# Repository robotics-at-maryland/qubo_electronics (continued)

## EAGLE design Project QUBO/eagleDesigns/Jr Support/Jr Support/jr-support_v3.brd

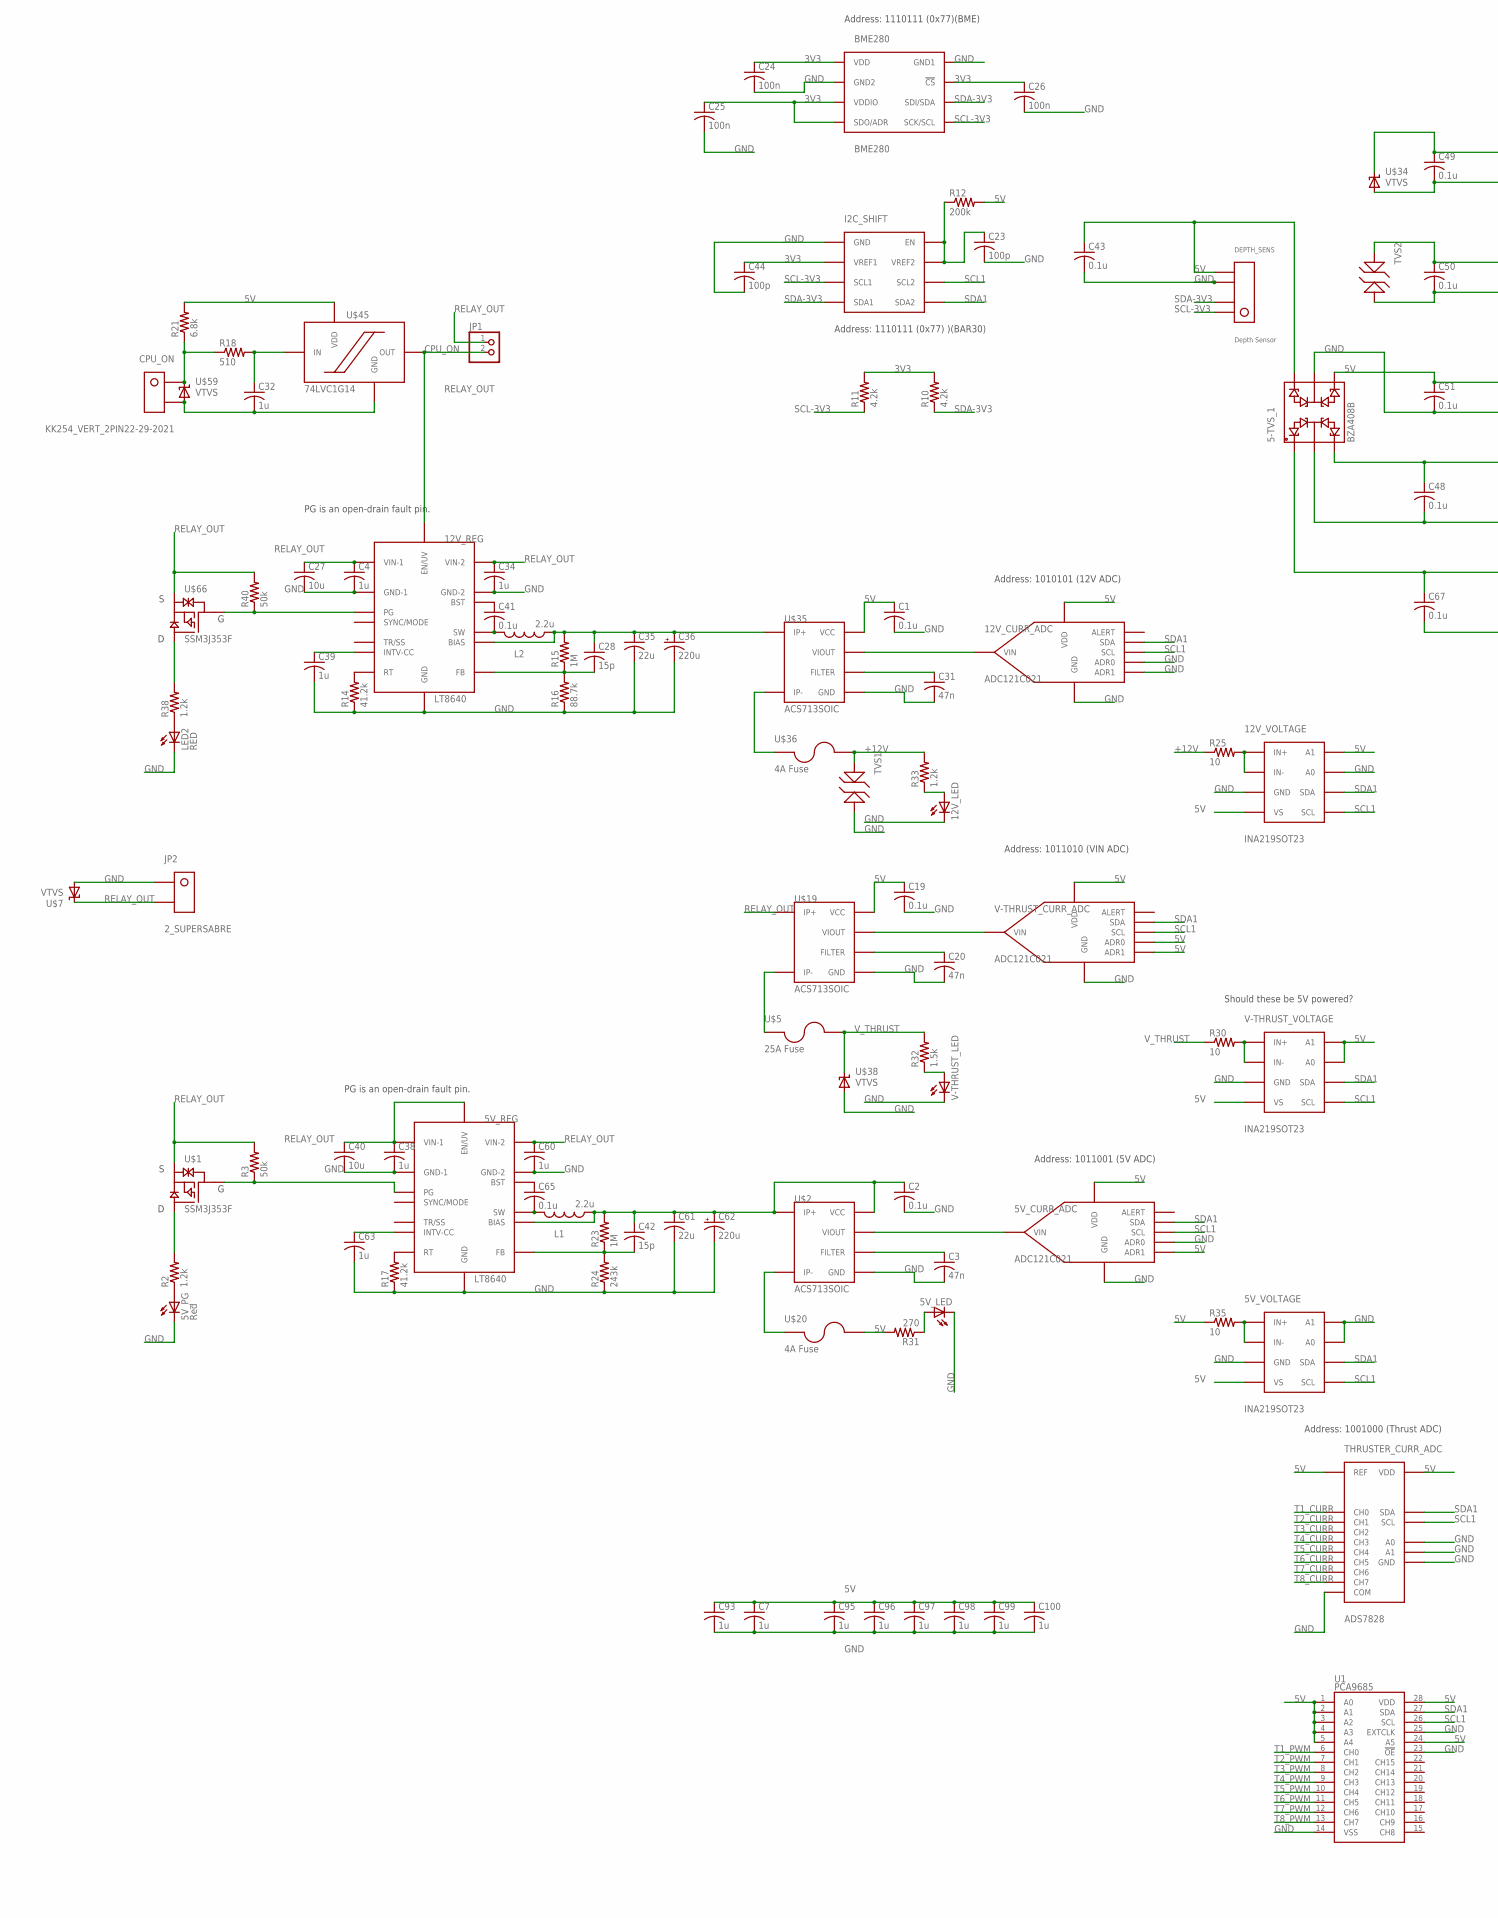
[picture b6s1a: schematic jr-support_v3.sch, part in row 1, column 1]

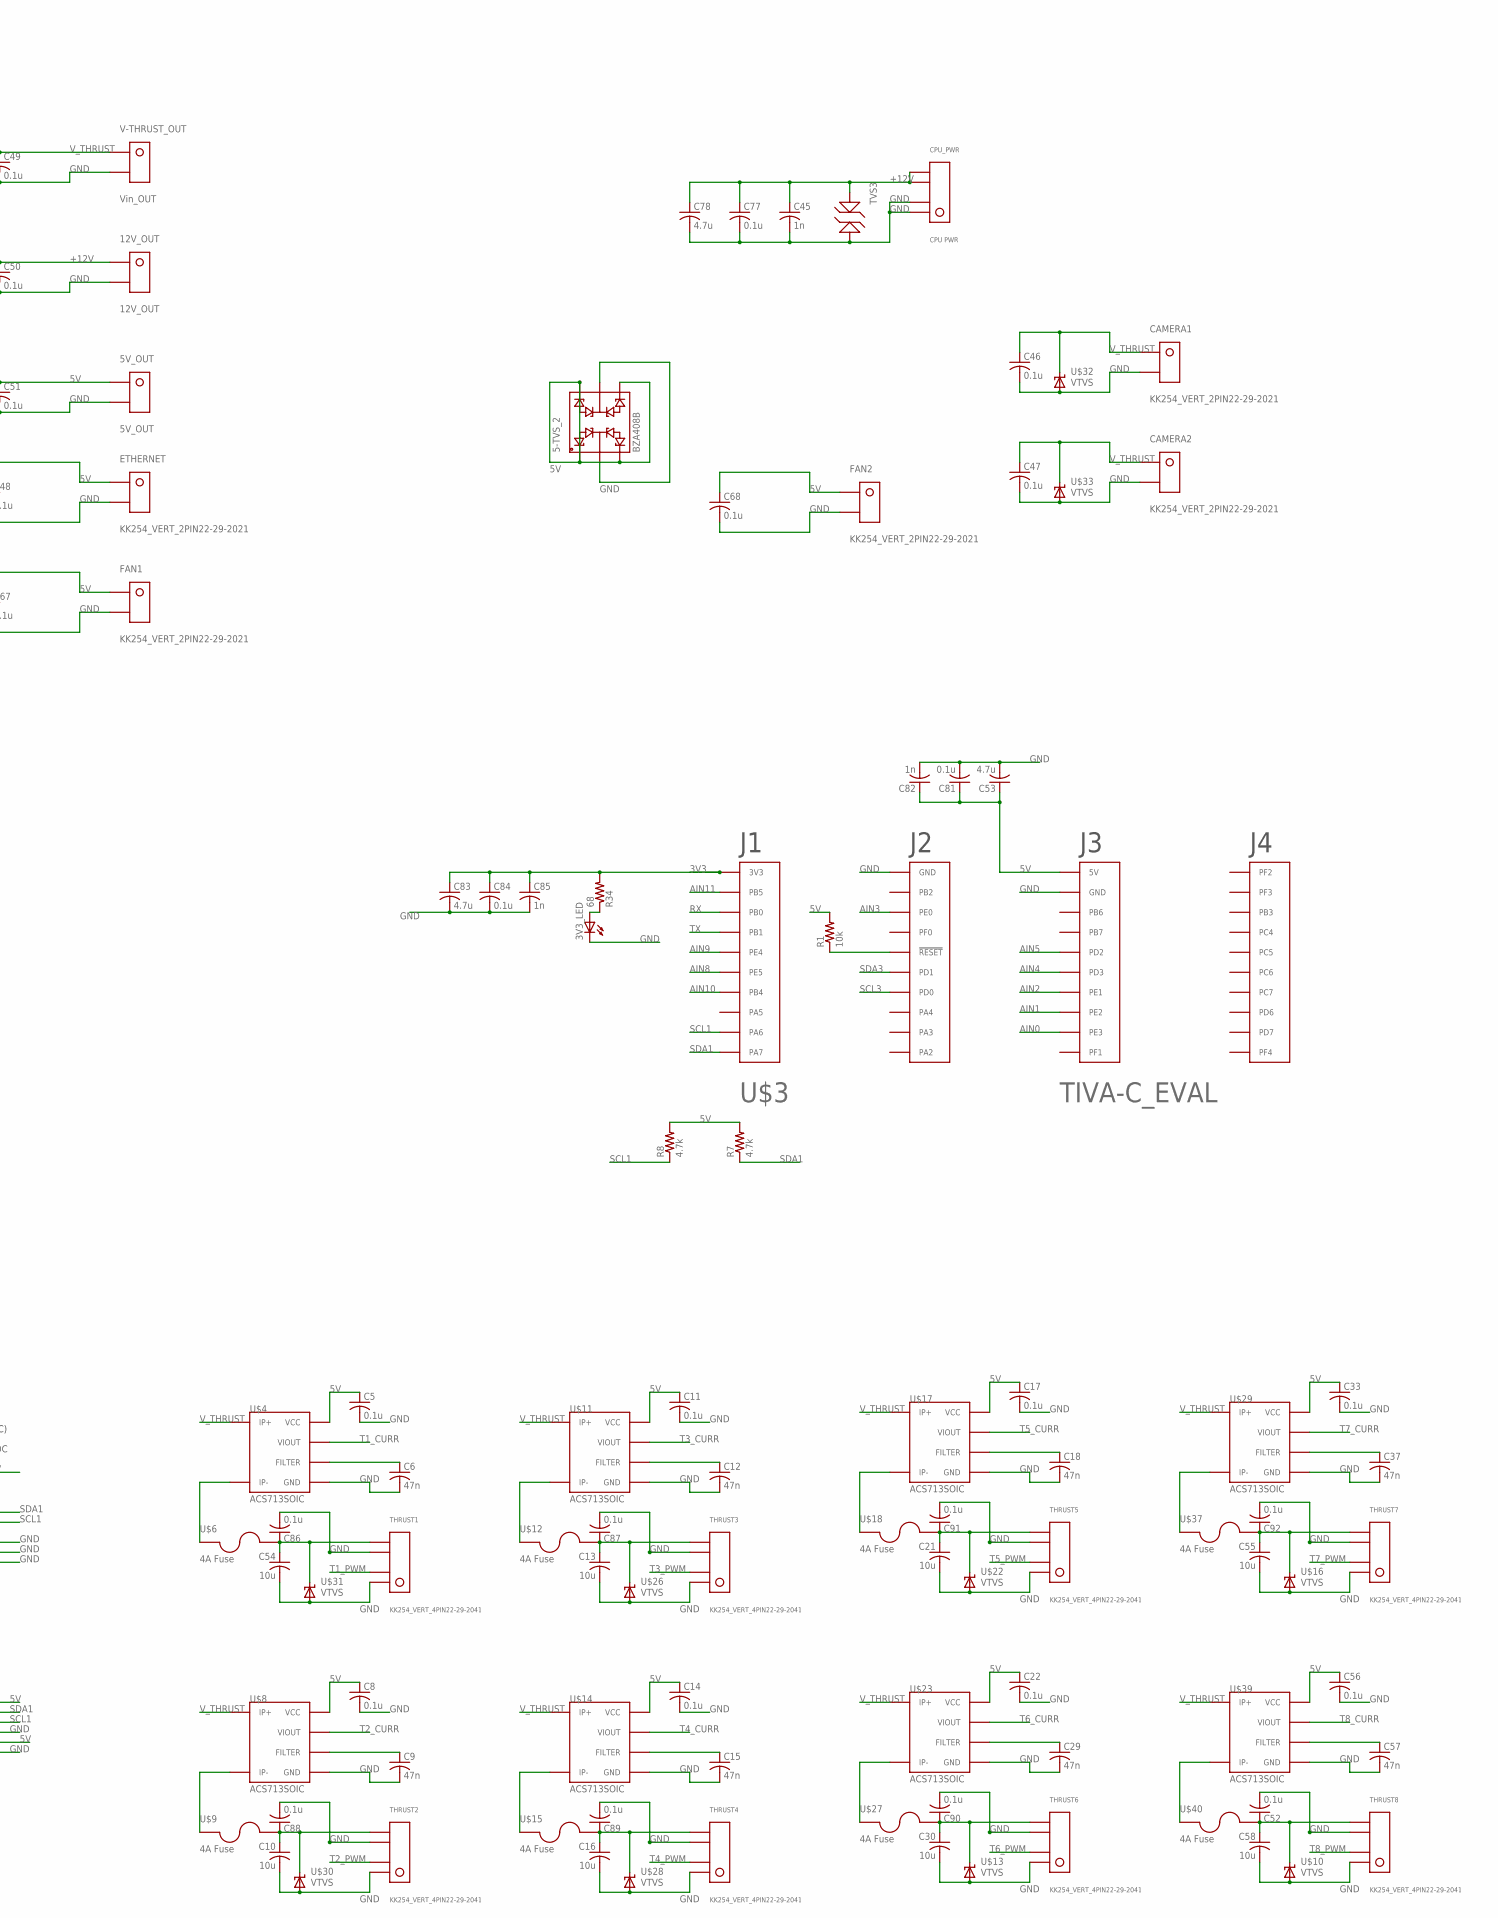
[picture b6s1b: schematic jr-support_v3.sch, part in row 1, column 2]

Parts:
3V3_LED, 5V_LED, 12V_LED: 0805_LED; 0805
5-TVS_1, 5-TVS_2: BZA408B; SOT457
5V_CURR_ADC, 12V_CURR_ADC: ADC121C021; VSSOP-8
5V_OUT: 5V_OUT; KK254_VERT_2PIN
5V_PG: Red; CHIP-LED0805
5V_REG, 12V_REG: LT8640; QFN18-3X4
5V_VOLTAGE, 12V_VOLTAGE: INA219SOT23; SOT-23-8
12V_OUT: 12V_OUT; KK254_VERT_2PIN
BME280: BME280; BME280_LGA
C1, C2, C5, C8, C11, C14, C17, C19, C22, C33, C41, C43, C46, C47, C48, C49, C50, C51, C52, C56, C65, C67, C68, C77, C81, C84, C86, C87, C88, C89, C90, C91, C92: 0.1u; C0805
C3, C6, C9, C12, C15, C18, C20, C29, C31, C37, C57: 47n; C0805
C4, C7, C32, C34, C38, C39, C60, C63, C93, C95, C96, C97, C98, C99, C100: 1u; C0805
C10, C13, C16, C21, C27, C30, C40, C54, C55, C58: 10u; C0805
C23, C44: 100p; C0805
C24, C25, C26: 100n; C0805
C28, C42: 15p; C0805
C35, C61: 22u; C0805
C36, C62: 220u; C-F80
C45, C82, C85: 1n; C0805
C53, C78, C83: 4.7u; C0805
CAMERA1, CAMERA2: KK254_VERT_2PIN22-29-2021; KK254_VERT_2PIN
CPU_ON: KK254_VERT_2PIN22-29-2021; KK254_VERT_2PIN
CPU_PWR: CPU PWR; KK254_VERT_4PIN
DEPTH_SENS: Depth Sensor; KK254_VERT_4PIN
ETHERNET: KK254_VERT_2PIN22-29-2021; KK254_VERT_2PIN
FAN1, FAN2: KK254_VERT_2PIN22-29-2021; KK254_VERT_2PIN
I2C_SHIFT: PCA9306DCT; SM8
JP1: PINHD-1X2; 1X02
JP2: 2_SUPERSABRE; SUPERSABRE_2CIRCUIT
L1, L2: 2.2u; L0740
LED2: RED; CHIP-LED0805
R1: 10k; R0805
R2, R33, R38: 1.2k; R0805
R3, R40: 50k; R0805
R7, R8: 4.7k; R0805
R10, R11: 4.2k; R0805
R12: 200k; R0805
R14, R17: 41.2k; R0805
R15, R23: 1M; R0805
R16: 88.7k; R0805
R18: 510; R0805
R21: 6.8k; R0805
R24: 243k; R0805
R25, R30, R35: 10; R0805
R31: 270; R0805
R32: 1.5k; R0805
R34: 68; R0805
THRUST1, THRUST2, THRUST3, THRUST4, THRUST5, THRUST6, THRUST7, THRUST8: KK254_VERT_4PIN22-29-2041; KK254_VERT_4PIN
THRUSTER_CURR_ADC: ADS7828; TSSOP16
TVS1, TVS2, TVS3: ESD12VD3B; SOD-323
U1: PCA9685; TSSOP-28_4MM
U$1, U$66: SSM3J353F; SOT-346-3/S-MINI
U$2, U$4, U$8, U$11, U$14, U$17, U$19, U$23, U$29, U$35, U$39: ACS713SOIC; ACS713-SOIC
U$3: TIVA-C_EVAL
U$5: 25A Fuse; 1.25"_FUSECLIPS
U$6, U$9, U$12, U$15, U$18, U$20, U$27, U$36, U$37, U$40: 4A Fuse; 154-OMNI-BLOK
U$7, U$10, U$13, U$16, U$22, U$26, U$28, U$30, U$31, U$32, U$33, U$34, U$38, U$59: VTVS; DO-219AB
U$45: 74LVC1G14; TSSOP5
V-THRUST_CURR_ADC: ADC121C021; VSSOP-8
V-THRUST_LED: 0805_LED; 0805
V-THRUST_OUT: Vin_OUT; KK254_VERT_2PIN
V-THRUST_VOLTAGE: INA219SOT23; SOT-23-8

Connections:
3V3: BME280.P$2 (!CS), BME280.P$5 (SDO/ADR), BME280.P$6 (VDDIO), BME280.P$8 (VDD), C24.1, C25.1, C26.1, C44.1, C83.1, C84.1, C85.1, I2C_SHIFT.P$2 (VREF1), R10.2, R11.2, R34.2, U$3.1-1 (3V3)
5V: 5-TVS_1.P$1, 5-TVS_1.P$3, 5-TVS_1.P$4, 5-TVS_1.P$6, 5-TVS_2.P$1, 5-TVS_2.P$3, 5-TVS_2.P$4, 5-TVS_2.P$6, 5V_CURR_ADC.P$5 (VDD), 5V_CURR_ADC.P$6 (ADR1), 5V_OUT.P$1, 5V_VOLTAGE.P$4 (VS), 12V_CURR_ADC.P$5 (VDD), 12V_VOLTAGE.P$4 (VS), 12V_VOLTAGE.P$8 (A1), C1.1, C5.1, C7.1, C8.1, C11.1, C14.1, C17.1, C19.1, C22.1, C33.1, C43.1, C48.1, C51.1, C53.1, C56.1, C67.1, C68.1, C81.1, C82.1, C93.1, C95.1, C96.1, C97.1, C98.1, C99.1, C100.1, DEPTH_SENS.P$4, ETHERNET.P$1, FAN1.P$1, FAN2.P$1, R1.2, R7.2, R8.2, R12.2, R21.2, R31.2, R35.1, THRUSTER_CURR_ADC.10 (REF), THRUSTER_CURR_ADC.16 (VDD), U1.1 (A0), U1.2 (A1), U1.3 (A2), U1.4 (A3), U1.5 (A4), U1.24 (A5), U1.28 (VDD), U$3.3-1 (5V), U$4.P$8 (VCC), U$8.P$8 (VCC), U$11.P$8 (VCC), U$14.P$8 (VCC), U$17.P$8 (VCC), U$19.P$8 (VCC), U$20.P$2, U$23.P$8 (VCC), U$29.P$8 (VCC), U$35.P$8 (VCC), U$39.P$8 (VCC), U$45.P$5 (VDD), V-THRUST_CURR_ADC.P$3 (ADR0), V-THRUST_CURR_ADC.P$5 (VDD), V-THRUST_CURR_ADC.P$6 (ADR1), V-THRUST_VOLTAGE.P$4 (VS), V-THRUST_VOLTAGE.P$7 (A0), V-THRUST_VOLTAGE.P$8 (A1)
+12V: 12V_OUT.P$1, C45.1, C50.1, C77.1, C78.1, CPU_PWR.P$3, CPU_PWR.P$4, R25.1, R33.2, TVS1.P$1, TVS2.P$1, TVS3.P$1, U$36.P$2
AIN0: U$3.3-9 (PE3)
AIN1: U$3.3-8 (PE2)
AIN2: U$3.3-7 (PE1)
AIN3: U$3.2-3 (PE0)
AIN4: U$3.3-6 (PD3)
AIN5: U$3.3-5 (PD2)
AIN8: U$3.1-6 (PE5)
AIN9: U$3.1-5 (PE4)
AIN10: U$3.1-7 (PB4)
AIN11: U$3.1-2 (PB5)
CPU_ON: 12V_REG.14 (EN/UV), JP1.2, U$45.P$4 (OUT)
GND: 3V3_LED.P$2 (C), 5-TVS_1.P$2, 5-TVS_1.P$5, 5-TVS_2.P$2, 5-TVS_2.P$5, 5V_CURR_ADC.P$3 (ADR0), 5V_CURR_ADC.P$7 (GND), 5V_LED.P$2 (C), 5V_OUT.P$2, 5V_PG.C, 5V_REG.6 (GND-1), 5V_REG.7 (GND-1), 5V_REG.10 (GND-2), 5V_REG.11 (GND-2), 5V_REG.18 (GND), 5V_VOLTAGE.P$3 (GND), 5V_VOLTAGE.P$7 (A0), 5V_VOLTAGE.P$8 (A1), 12V_CURR_ADC.P$3 (ADR0), 12V_CURR_ADC.P$6 (ADR1), 12V_CURR_ADC.P$7 (GND), 12V_LED.P$2 (C), 12V_OUT.P$2, 12V_REG.6 (GND-1), 12V_REG.7 (GND-1), 12V_REG.10 (GND-2), 12V_REG.11 (GND-2), 12V_REG.18 (GND), 12V_VOLTAGE.P$3 (GND), 12V_VOLTAGE.P$7 (A0), BME280.P$1 (GND1), BME280.P$7 (GND2), C1.2, C2.2, C3.2, C4.2, C5.2, C6.2, C7.2, C8.2, C9.2, C10.2, C11.2, C12.2, C13.2, C14.2, C15.2, C16.2, C17.2, C18.2, C19.2, C20.2, C21.2, C22.2, C23.2, C24.2, C25.2, C26.2, C27.2, C29.2, C30.2, C31.2, C32.2, C33.2, C34.2, C35.2, C36.P$2 (-), C37.2, C38.2, C39.2, C40.2, C43.2, C44.2, C45.2, C46.2, C47.2, C48.2, C49.2, C50.2, C51.2, C52.2, C53.2, C54.2, C55.2, C56.2, C57.2, C58.2, C60.2, C61.2, C62.P$2 (-), C63.2, C67.2, C68.2, C77.2, C78.2, C81.2, C82.2, C83.2, C84.2, C85.2, C86.2, C87.2, C88.2, C89.2, C90.2, C91.2, C92.2, C93.2, C95.2, C96.2, C97.2, C98.2, C99.2, C100.2, CAMERA1.P$2, CAMERA2.P$2, CPU_ON.P$2, CPU_PWR.P$1, CPU_PWR.P$2, DEPTH_SENS.P$3, ETHERNET.P$2, FAN1.P$2, FAN2.P$2, I2C_SHIFT.P$1 (GND), JP2.P$1, LED2.C, R14.1, R16.1, R17.1, R24.1, THRUST1.P$1, THRUST1.P$3, THRUST2.P$1, THRUST2.P$3, THRUST3.P$1, THRUST3.P$3, THRUST4.P$1, THRUST4.P$3, THRUST5.P$1, THRUST5.P$3, THRUST6.P$1, THRUST6.P$3, THRUST7.P$1, THRUST7.P$3, THRUST8.P$1, THRUST8.P$3, THRUSTER_CURR_ADC.9 (GND), THRUSTER_CURR_ADC.11 (COM), THRUSTER_CURR_ADC.12 (A0), THRUSTER_CURR_ADC.13 (A1), TVS1.P$2, TVS2.P$2, TVS3.P$2, U1.14 (VSS), U1.23 (!OE), U1.25 (EXTCLK), U$2.P$5 (GND), U$3.2-1 (GND), U$3.3-2 (GND), U$4.P$5 (GND), U$7.P$1 (A), U$8.P$5 (GND), U$10.P$1 (A), U$11.P$5 (GND), U$13.P$1 (A), U$14.P$5 (GND), U$16.P$1 (A), U$17.P$5 (GND), U$19.P$5 (GND), U$22.P$1 (A), U$23.P$5 (GND), U$26.P$1 (A), U$28.P$1 (A), U$29.P$5 (GND), U$30.P$1 (A), U$31.P$1 (A), U$32.P$1 (A), U$33.P$1 (A), U$34.P$1 (A), U$35.P$5 (GND), U$38.P$1 (A), U$39.P$5 (GND), U$45.P$3 (GND), U$59.P$1 (A), V-THRUST_CURR_ADC.P$7 (GND), V-THRUST_LED.P$2 (C), V-THRUST_OUT.P$2, V-THRUST_VOLTAGE.P$3 (GND)
unnamed: 12V_REG.15 (RT), R14.2
unnamed: R1.1, U$3.2-5 (!RESET!)
unnamed: 5V_PG.A, R2.1
unnamed: R2.2, U$1.P$2 (D)
unnamed: 5V_REG.19 (PG), R3.1, U$1.P$1 (G)
unnamed: 12V_REG.1 (BIAS), C28.1, C35.1, C36.P$1 (+), L2.P$2 (2), R15.2, U$35.P$1 (IP+), U$35.P$2 (IP+)
unnamed: 5V_REG.15 (RT), R17.2
unnamed: C3.1, U$2.P$6 (FILTER)
unnamed: C9.1, U$8.P$6 (FILTER)
unnamed: C6.1, U$4.P$6 (FILTER)
unnamed: C54.1, C86.1, THRUST1.P$4, U$6.P$2, U$31.P$2 (C)
unnamed: U$4.P$3 (IP-), U$4.P$4 (IP-), U$6.P$1
unnamed: C10.1, C88.1, THRUST2.P$4, U$9.P$2, U$30.P$2 (C)
unnamed: U$8.P$3 (IP-), U$8.P$4 (IP-), U$9.P$1
unnamed: C12.1, U$11.P$6 (FILTER)
unnamed: C13.1, C87.1, THRUST3.P$4, U$12.P$2, U$26.P$2 (C)
unnamed: U$11.P$3 (IP-), U$11.P$4 (IP-), U$12.P$1
unnamed: C15.1, U$14.P$6 (FILTER)
unnamed: C16.1, C89.1, THRUST4.P$4, U$15.P$2, U$28.P$2 (C)
unnamed: U$14.P$3 (IP-), U$14.P$4 (IP-), U$15.P$1
unnamed: C18.1, U$17.P$6 (FILTER)
unnamed: C21.1, C91.1, THRUST5.P$4, U$18.P$2, U$22.P$2 (C)
unnamed: U$17.P$3 (IP-), U$17.P$4 (IP-), U$18.P$1
unnamed: C29.1, U$23.P$6 (FILTER)
unnamed: C30.1, C90.1, THRUST6.P$4, U$13.P$2 (C), U$27.P$2
unnamed: U$23.P$3 (IP-), U$23.P$4 (IP-), U$27.P$1
unnamed: C37.1, U$29.P$6 (FILTER)
unnamed: 12V_REG.8 (SW), 12V_REG.9 (SW), 12V_REG.21 (SW), 12V_REG.22 (SW), C41.2, L2.P$1 (1)
unnamed: C20.1, U$19.P$6 (FILTER)
unnamed: U$5.P$1, U$5.P$2, U$19.P$3 (IP-), U$19.P$4 (IP-)
unnamed: C55.1, C92.1, THRUST7.P$4, U$16.P$2 (C), U$37.P$2
unnamed: U$29.P$3 (IP-), U$29.P$4 (IP-), U$37.P$1
unnamed: C57.1, U$39.P$6 (FILTER)
unnamed: C52.1, C58.1, THRUST8.P$4, U$10.P$2 (C), U$40.P$2
unnamed: 5V_REG.8 (SW), 5V_REG.9 (SW), 5V_REG.21 (SW), 5V_REG.22 (SW), C65.2, L1.P$1 (1)
unnamed: C23.1, I2C_SHIFT.P$7 (VREF2), I2C_SHIFT.P$8 (EN), R12.1
unnamed: 5V_REG.20 (FB), C42.2, R23.1, R24.2
unnamed: 5V_REG.3 (BST), C65.1
unnamed: 12V_REG.20 (FB), C28.2, R15.1, R16.2
unnamed: 12V_REG.3 (BST), C41.1
unnamed: U$39.P$3 (IP-), U$39.P$4 (IP-), U$40.P$1
unnamed: 5V_REG.2 (INTV-CC), C63.1
unnamed: 12V_VOLTAGE.P$1 (IN+), 12V_VOLTAGE.P$2 (IN-), R25.2
unnamed: C31.1, U$35.P$6 (FILTER)
unnamed: U$19.P$7 (VIOUT), V-THRUST_CURR_ADC.P$4 (VIN)
unnamed: 12V_REG.2 (INTV-CC), C39.1
unnamed: U$2.P$3 (IP-), U$2.P$4 (IP-), U$20.P$1
unnamed: U$35.P$3 (IP-), U$35.P$4 (IP-), U$36.P$1
unnamed: 5V_CURR_ADC.P$4 (VIN), U$2.P$7 (VIOUT)
unnamed: R30.2, V-THRUST_VOLTAGE.P$1 (IN+), V-THRUST_VOLTAGE.P$2 (IN-)
unnamed: C32.1, R18.2, U$45.P$2 (IN)
unnamed: 12V_CURR_ADC.P$4 (VIN), U$35.P$7 (VIOUT)
unnamed: CPU_ON.P$1, R18.1, R21.1, U$59.P$2 (C)
unnamed: 5V_LED.P$1 (A), R31.1
unnamed: R32.1, V-THRUST_LED.P$1 (A)
unnamed: 12V_LED.P$1 (A), R33.1
unnamed: 3V3_LED.P$1 (A), R34.1
unnamed: 5V_VOLTAGE.P$1 (IN+), 5V_VOLTAGE.P$2 (IN-), R35.2
unnamed: LED2.A, R38.1
unnamed: R38.2, U$66.P$2 (D)
unnamed: 12V_REG.19 (PG), R40.1, U$66.P$1 (G)
RELAY_OUT: 5V_REG.4 (VIN-1), 5V_REG.13 (VIN-2), 5V_REG.14 (EN/UV), 12V_REG.4 (VIN-1), 12V_REG.13 (VIN-2), C4.1, C27.1, C34.1, C38.1, C40.1, C60.1, JP1.1, JP2.P$2, R3.2, R40.2, U$1.P$3 (S), U$7.P$2 (C), U$19.P$1 (IP+), U$19.P$2 (IP+), U$66.P$3 (S)
RX: U$3.1-3 (PB0)
SCL1: 5V_CURR_ADC.P$1 (SCL), 5V_VOLTAGE.P$5 (SCL), 12V_CURR_ADC.P$1 (SCL), 12V_VOLTAGE.P$5 (SCL), I2C_SHIFT.P$6 (SCL2), R8.1, THRUSTER_CURR_ADC.14 (SCL), U1.26 (SCL), U$3.1-9 (PA6), V-THRUST_CURR_ADC.P$1 (SCL), V-THRUST_VOLTAGE.P$5 (SCL)
SCL3: U$3.2-7 (PD0)
SCL-3V3: BME280.P$4 (SCK/SCL), DEPTH_SENS.P$1, I2C_SHIFT.P$3 (SCL1), R11.1
SDA1: 5V_CURR_ADC.P$8 (SDA), 5V_VOLTAGE.P$6 (SDA), 12V_CURR_ADC.P$8 (SDA), 12V_VOLTAGE.P$6 (SDA), I2C_SHIFT.P$5 (SDA2), R7.1, THRUSTER_CURR_ADC.15 (SDA), U1.27 (SDA), U$3.1-10 (PA7), V-THRUST_CURR_ADC.P$8 (SDA), V-THRUST_VOLTAGE.P$6 (SDA)
SDA3: U$3.2-6 (PD1)
SDA-3V3: BME280.P$3 (SDI/SDA), DEPTH_SENS.P$2, I2C_SHIFT.P$4 (SDA1), R10.1
SW-5V: 5V_REG.1 (BIAS), C2.1, C42.1, C61.1, C62.P$1 (+), L1.P$2 (2), R23.2, U$2.P$1 (IP+), U$2.P$2 (IP+), U$2.P$8 (VCC)
T1_CURR: THRUSTER_CURR_ADC.1 (CH0), U$4.P$7 (VIOUT)
T1_PWM: THRUST1.P$2, U1.6 (CH0)
T2_CURR: THRUSTER_CURR_ADC.2 (CH1), U$8.P$7 (VIOUT)
T2_PWM: THRUST2.P$2, U1.7 (CH1)
T3_CURR: THRUSTER_CURR_ADC.3 (CH2), U$11.P$7 (VIOUT)
T3_PWM: THRUST3.P$2, U1.8 (CH2)
T4_CURR: THRUSTER_CURR_ADC.4 (CH3), U$14.P$7 (VIOUT)
T4_PWM: THRUST4.P$2, U1.9 (CH3)
T5_CURR: THRUSTER_CURR_ADC.5 (CH4), U$17.P$7 (VIOUT)
T5_PWM: THRUST5.P$2, U1.10 (CH4)
T6_CURR: THRUSTER_CURR_ADC.6 (CH5), U$23.P$7 (VIOUT)
T6_PWM: THRUST6.P$2, U1.11 (CH5)
T7_CURR: THRUSTER_CURR_ADC.7 (CH6), U$29.P$7 (VIOUT)
T7_PWM: THRUST7.P$2, U1.12 (CH6)
T8_CURR: THRUSTER_CURR_ADC.8 (CH7), U$39.P$7 (VIOUT)
T8_PWM: THRUST8.P$2, U1.13 (CH7)
TX: U$3.1-4 (PB1)
V_THRUST: C46.1, C47.1, C49.1, CAMERA1.P$1, CAMERA2.P$1, R30.1, R32.2, U$4.P$1 (IP+), U$4.P$2 (IP+), U$5.P$3, U$5.P$4, U$8.P$1 (IP+), U$8.P$2 (IP+), U$11.P$1 (IP+), U$11.P$2 (IP+), U$14.P$1 (IP+), U$14.P$2 (IP+), U$17.P$1 (IP+), U$17.P$2 (IP+), U$23.P$1 (IP+), U$23.P$2 (IP+), U$29.P$1 (IP+), U$29.P$2 (IP+), U$32.P$2 (C), U$33.P$2 (C), U$34.P$2 (C), U$38.P$2 (C), U$39.P$1 (IP+), U$39.P$2 (IP+), V-THRUST_OUT.P$1

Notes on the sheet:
Address: 1110111 (0x77)(BME)
Address: 1001000 (Thrust ADC)
Address: 1110111 (0x77) )(BAR30)
Address: 1010101 (12V ADC)
Address: 1011010 (VIN ADC)
Address: 1011001 (5V ADC)
PG is an open-drain fault pin.
Should these be 5V powered?

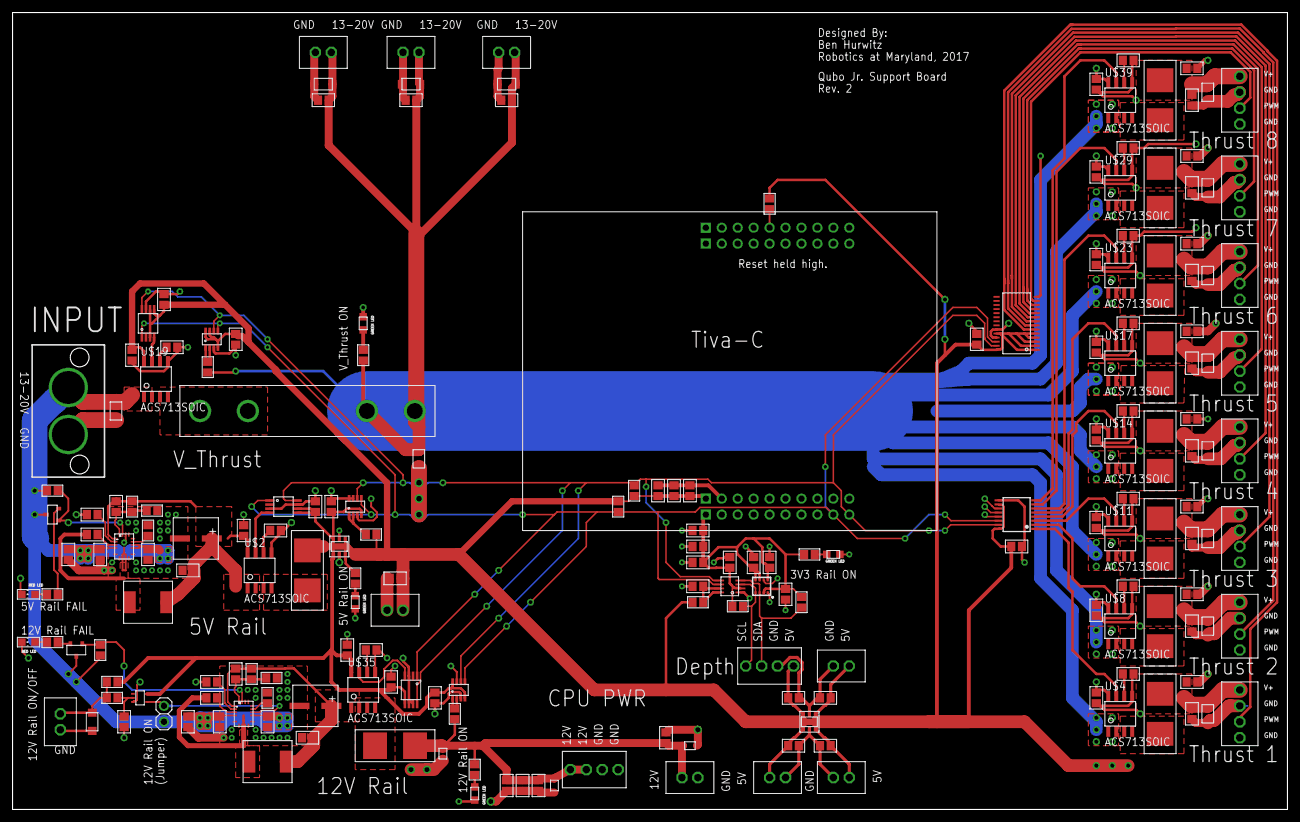
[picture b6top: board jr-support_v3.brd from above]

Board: 2 copper layers, 203.2 x 127.0 mm, 197 parts (0 on the bottom side), 89 nets.

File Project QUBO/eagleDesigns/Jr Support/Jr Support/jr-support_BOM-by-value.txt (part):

Partlist exported from C:/Users/Ben/Documents/Dropbox/UMD/R@M/RAM Tran Electronics_2016/qubo_electronics.git/Project QUBO/eagleDesigns/Jr Support/Jr Support/jr-support_v3.sch at Wed, 6/14/2017 1:37 PM

Qty Value                     Device                    Package             Parts                                                                                                                                                           Description                                                                               PROD_ID  VALUE  
4                             0805_LED                  0805                3V3_LED, 5V_LED, 12V_LED, V-THRUST_LED                                                                                                                          LED, 0805 package. Any variety.                                                                           
3                             ESD12VD3B                 SOD-323             TVS1, TVS2, TVS3                                                                                                                                                MC Semi ESD12VD3B                                                                                         
1                             PCA9306DCT                SM8                 I2C_SHIFT                                                                                                                                                       TI I2C/SMBus Level Shifter                                                                                
1                             PINHD-1X2                 1X02                JP1                                                                                                                                                             PIN HEADER                                                                                                
33  0.1u                      C-USC0805                 C0805               C1, C2, C5, C8, C11, C14, C17, C19, C22, C33, C41, C43, C46, C47, C48, C49, C50, C51, C52, C56, C65, C67, C68, C77, C81, C84, C86, C87, C88, C89, C90, C91, C92 CAPACITOR, American symbol                                                                                
3   1.2k                      R-US_R0805                R0805               R2, R33, R38                                                                                                                                                    RESISTOR, American symbol                                                                                 
1   1.5k                      R-US_R0805                R0805               R32                                                                                                                                                             RESISTOR, American symbol                                                                                 
3   10                        R-US_R0805                R0805               R25, R30, R35                                                                                                                                                   RESISTOR, American symbol                                                                                 
3   100n                      C-USC0805                 C0805               C24, C25, C26                                                                                                                                                   CAPACITOR, American symbol                                                                                
2   100p                      C-USC0805                 C0805               C23, C44                                                                                                                                                        CAPACITOR, American symbol                                                                                
1   10k                       R-US_R0805                R0805               R1                                                                                                                                                              RESISTOR, American symbol                                                                                 
10  10u                       C-USC0805                 C0805               C10, C13, C16, C21, C27, C30, C40, C54, C55, C58                                                                                                                CAPACITOR, American symbol                                                                                
1   12V_OUT                   KK254_VERT_2PIN22-29-2021 KK254_VERT_2PIN     12V_OUT                                                                                                                                                         KK® 254 Wire-to-Board Header, Vertical, with Friction Lock, 2 Circuits, Gold (Au) Plating                 
2   15p                       C-USC0805                 C0805               C28, C42                                                                                                                                                        CAPACITOR, American symbol                                                                                
2   1M                        R-US_R0805                R0805               R15, R23                                                                                                                                                        RESISTOR, American symbol                                                                                 
3   1n                        C-USC0805                 C0805               C45, C82, C85                                                                                                                                                   CAPACITOR, American symbol                                                                                
15  1u                        C-USC0805                 C0805               C4, C7, C32, C34, C38, C39, C60, C63, C93, C95, C96, C97, C98, C99, C100                                                                                        CAPACITOR, American symbol                                                                                
2   2.2u                      L-USL0740                 L0740               L1, L2                                                                                                                                                          INDUCTOR, American symbol                                                                                 
1   200k                      R-US_R0805                R0805               R12                                                                                                                                                             RESISTOR, American symbol                                                                                 
2   220u                      CPOL-USC-F80              C-F80               C36, C62                                                                                                                                                        POLARIZED CAPACITOR, American symbol                                                                      
2   22u                       C-USC0805                 C0805               C35, C61                                                                                                                                                        CAPACITOR, American symbol                                                                                
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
